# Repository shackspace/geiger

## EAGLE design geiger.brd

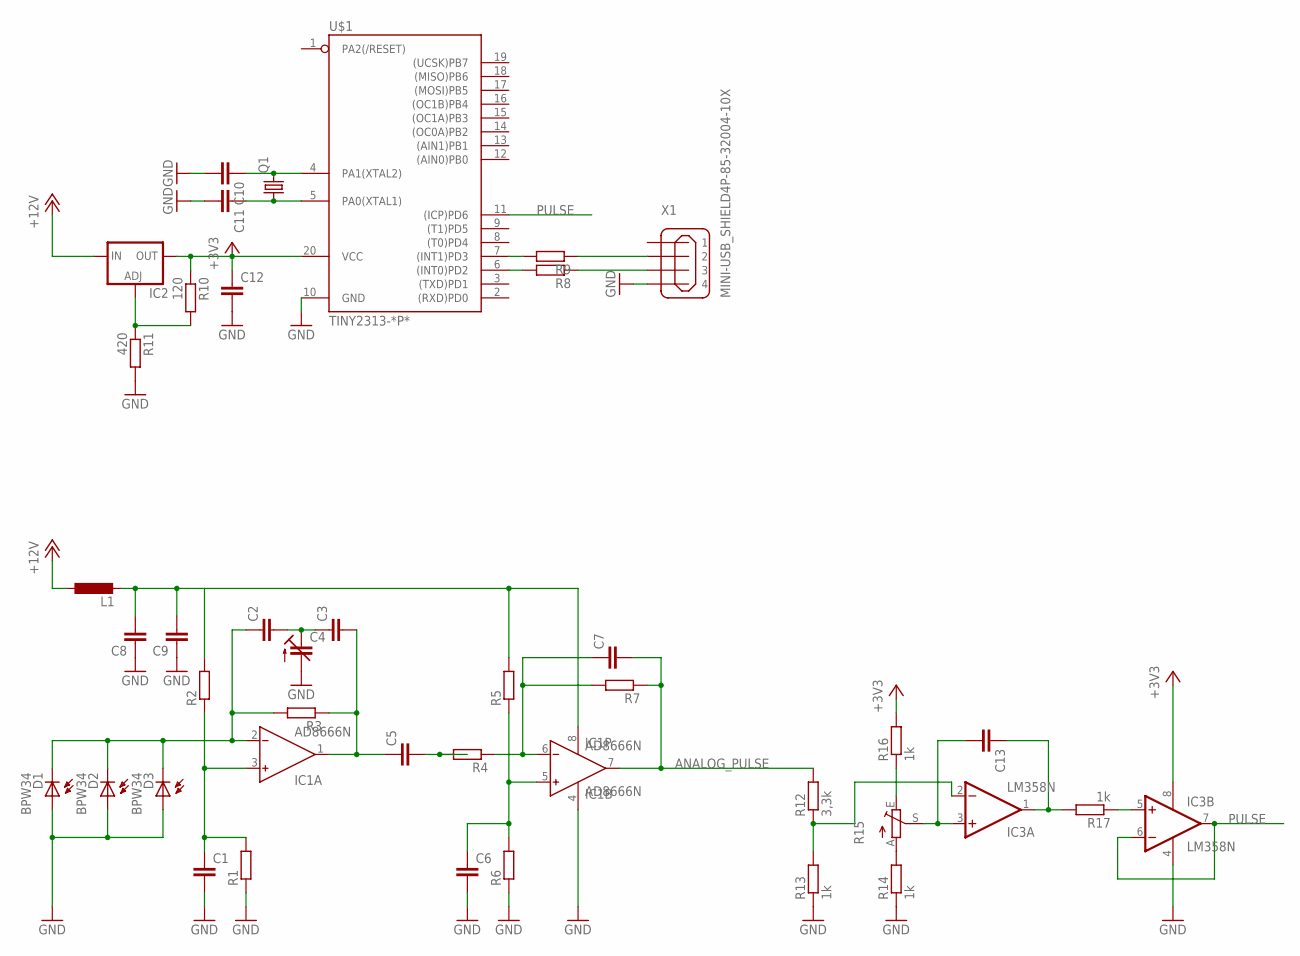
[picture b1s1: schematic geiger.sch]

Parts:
C1, C2, C3, C5, C6, C7, C8, C9, C10, C11, C12, C13: C-EU025-025X050; C025-025X050
C4: C-TRIMM3050.504; CTRIM3050.504
D1, D2, D3: BPW34; BPW32
IC1: AD8666N; DIL08
IC2: LM317L; 317L
IC3: LM358N; DIL08
L1: L-EU2200-12.7; 2200-12.7
Q1: CRYSTALHC49S; HC49/S
R1, R2, R3, R4, R5, R6, R7, R8, R9: R-EU_0207/7; 0207/7
R10: 120; 0207/7
R11: 420; 0207/7
R12: 3,3k; 0207/7
R13, R14, R16, R17: 1k; 0207/7
R15: TRIM_EU-LI10; LI10
U$1: TINY2313-*P*; DIL20
X1: MINI-USB_SHIELD4P-85-32004-10X; 85-32004-10X

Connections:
+3V3: C12.1, IC2.2 (OUT), IC3.8 (V+), R10.1, R16.2, U$1.20 (VCC)
+12V: IC2.3 (IN), L1.1
ANALOG_PULSE: C7.2, IC1.7 (OUT), R7.1, R12.2
GND: C1.2, C4.2 (A), C6.2, C8.1, C9.1, C10.2, C11.2, C12.2, D1.A, D2.A, D3.A, IC1.4 (V-), IC3.4 (V-), R1.1, R6.1, R11.2, R13.1, R14.1, U$1.10 (GND), X1.4
unnamed: C3.2, C5.1, IC1.1 (OUT), R3.1
unnamed: C2.1, D1.K (C), D2.K (C), D3.K (C), IC1.2 (IN-), R3.2
unnamed: C2.2, C3.1, C4.1 (E)
unnamed: C1.1, IC1.3 (IN+), R1.2, R2.1
unnamed: C10.1, Q1.2, U$1.4 (PA1(XTAL2))
unnamed: C5.2, R4.2
unnamed: C7.1, IC1.6 (IN-), R4.1, R7.2
unnamed: C6.1, IC1.5 (IN+), R5.1, R6.2
unnamed: C11.1, Q1.1, U$1.5 (PA0(XTAL1))
unnamed: R8.2, U$1.6 ((INT0)PD2)
unnamed: R9.2, U$1.7 ((INT1)PD3)
unnamed: C8.2, C9.2, IC1.8 (V+), L1.2, R2.2, R5.2
unnamed: R9.1, X1.2
unnamed: R8.1, X1.3
unnamed: IC2.1 (ADJ), R10.2, R11.1
unnamed: R14.2, R15.A
unnamed: IC3.2 (-IN), R12.1, R13.2
unnamed: R15.E, R16.1
unnamed: C13.2, IC3.3 (+IN), R15.S
unnamed: C13.1, IC3.1 (OUT), R17.2
unnamed: IC3.5 (+IN), R17.1
PULSE: IC3.6 (-IN), IC3.7 (OUT), U$1.11 ((ICP)PD6)

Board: 2 copper layers, 40 parts (0 on the bottom side), 26 nets, no tracks yet.

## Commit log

2014-02-14 added schematic + layout
2014-02-14 comperator added
